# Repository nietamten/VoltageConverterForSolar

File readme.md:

Kicad project of NCP1034 based buck converter with features useful for solar panels and batteries.

After adjusting compensation network with "Design Spreadsheet for NCP1034" seems to be stable  
If it's not, see troubleshooting section.

There is separate output anode with current limit. It can be used simultaneously with that not limited.
For example battery can be charged with limiting (to not damage it by overcurrent) and some device can use non-limited anode to not distgurb charging.
It is not working ideally (limited output can limit that not limited) but can be helpfull.

Minimum input voltage limit can increase output power by keeping solar panels near maximum power point.
It can be regulated by applying load higher than solar panels power (or when panel are no well illuminated, but not too low illuminated because looses on BD911 regulator becomes dominant and then input voltages lower than at power point gives more power on output) and measuring output power.
Limiting screw should stay in position where power is highest.

NCP1034 have max 80% PWM duty cycle, all power can not pass throw.
Output diodes (D6 and D9) can be replaced with wire, but then converter allows power to flow in reverse direction. When there is no input volatge and on output is battery, battery can charge input capacitors and power on converter and cause losses. 

Assembly notices:
- read NCP1034 datasheet and use xls "design worksheet"
- BD911 gives off a lot of heat, don't ommit radiator, it will be damaged on 15V supply overload
For testing, when short circuits are possible, raplace BD911 based regulator with some other, more failproof
for example LM5008 based converter. Using LM5008 also significantly reduces heat of whole device on light loads.
- do not ommit 3x100nF capacitors on imput, it can cause instability
- current sensing resistor (R13, R16) limits maximum current, use lower resistance when more current is needed to not burn it
- RT pin resistor (R7) was tested between 22k and 47k (90-180kHz), lower resistance (higher frequency) makes more heat on NCP1034, BD911 and AOB414 but seems to improve stability
(I have oversized inductor). Setting too high frequency can very fast cause overheat and damage to NCP1034.
- Touching working converter parts near NCP1034 (for example to check heating) can easily cause damage of NCP1034 and AOB414. Especially overcurrent and soft start circuits.
- do not mount parts without values, for exaple C21

Troubleshooting:
- converter is oscillating fast (there is output power)
  - increase input capacity
  - add low ESR capacitors on input, for example ceramic
  - change frequency (R7)
- converter is oscillating slower (a little or no power on output)
  - decrease output capacity to prevent over current
  - increase current limit (decrease R11), 5k seems to be safe
  - decrease output volage
- converter is oscillating when minimum voltage limit is working
  - try increase C19 or C18
- converter is oscillating when current limiter is working
  - try increase C16 or experiment with C22
- devices near converter stops working (usb mouse)
  - use ferrite filters on input and output
 
Testing  
Device was tested with 4x parallel 75W 91VOC 67VMP solar panels on long wires.
The load was little 24V 300W water heater.
The heater was left on the whole sunny day in room temperature and stay not damagd.
Voltage on output was for some time about 27V so I suspect that it was more than 300W.
AOB414, BD911 and NCP1034 was very hot but below 100C. I'm not sure it can survive that load in higher ambient temperature.
With lighter loads (I'm guessing about 200W) BD911 is hottest. With LM5008 whole converter is only a little warm.

There is not completed automatic maximum power point tracking extension board with some measurments on UART 

V2 tagged version is better for self-made PCB's but have mistake - no resistor at output of  max input voltage limiting opamp.
V3 tagged verion is for PCB's with metalized holes, radiator for transistors can be on second PCB side.

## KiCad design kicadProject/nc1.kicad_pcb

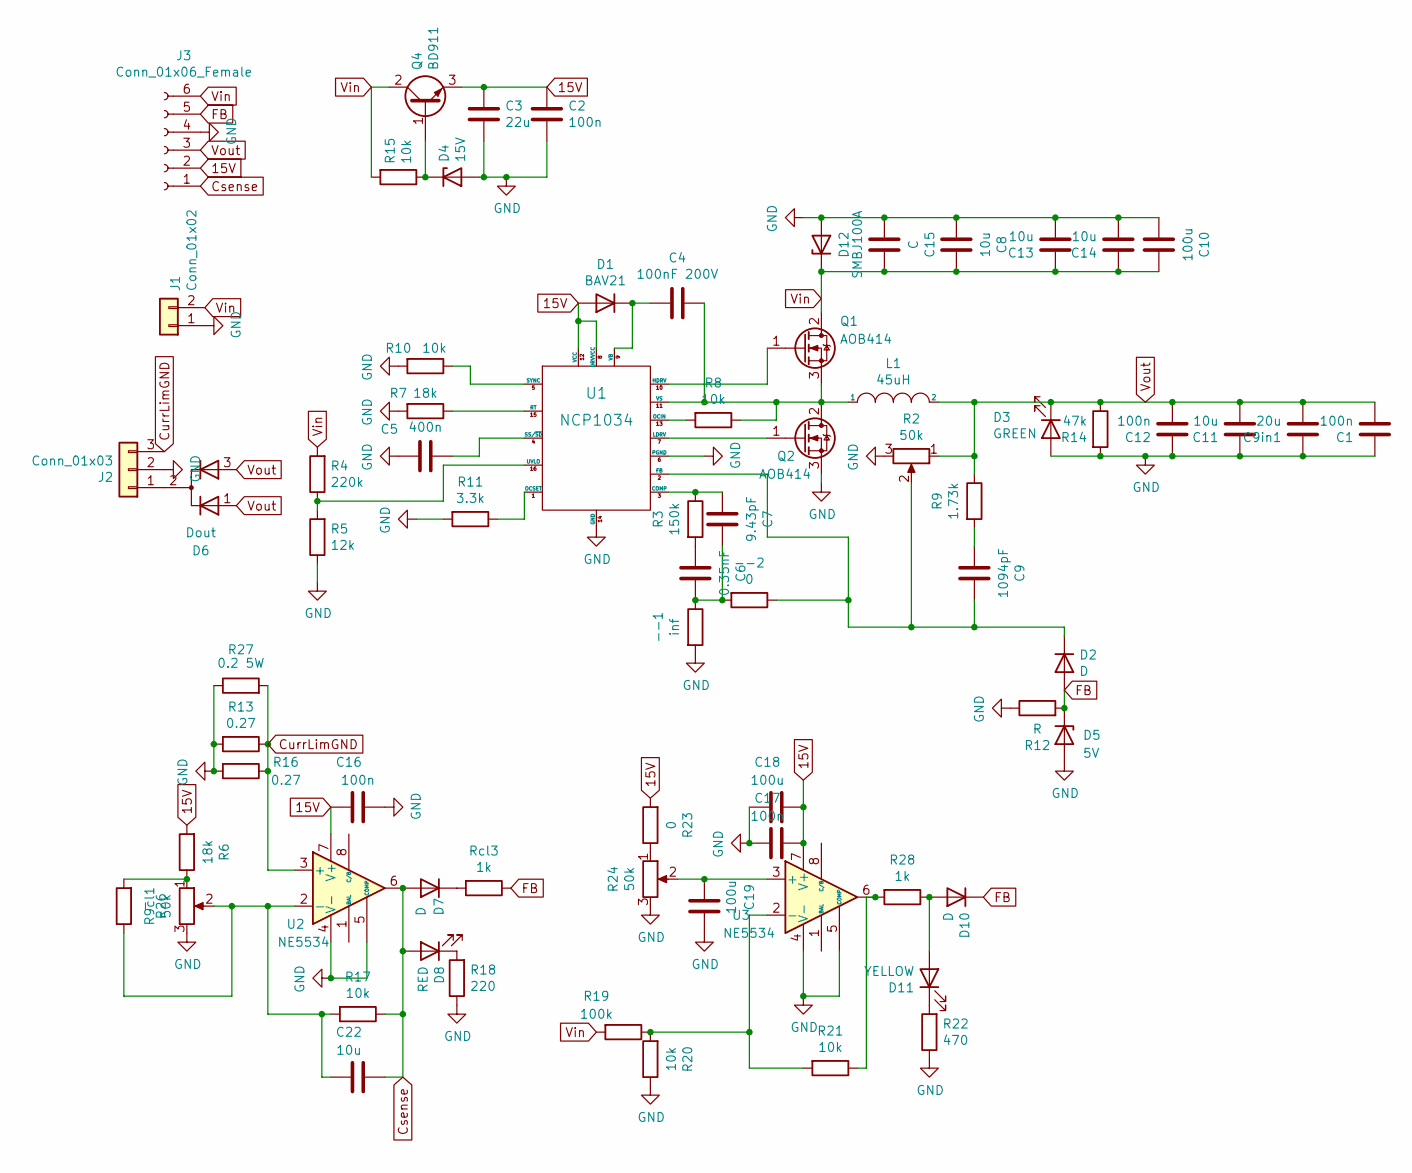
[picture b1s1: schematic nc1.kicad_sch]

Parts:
--1: inf; R_1206_3216Metric_Pad1.30x1.75mm_HandSolder
--2: 0; R_1206_3216Metric_Pad1.30x1.75mm_HandSolder
C1: 100n; CP_Radial_D18.0mm_P7.50mm
C2: 100n; C_1206_3216Metric
C3: 22u; C_1206_3216Metric
C4: 100nF 200V; C_2220_5650Metric
C5: 400n; C_1206_3216Metric_Pad1.42x1.75mm_HandSolder
C6: 0.35nF; C_1206_3216Metric_Pad1.42x1.75mm_HandSolder
C7: 9.43pF; C_1206_3216Metric_Pad1.42x1.75mm_HandSolder
C8: 10u; C_Rect_L7.0mm_W2.5mm_P5.00mm
C9: 1094pF; C_1206_3216Metric_Pad1.33x1.80mm_HandSolder
C9in1: 20u; C_Rect_L7.0mm_W2.5mm_P5.00mm
C10: 100u; C_Rect_L7.0mm_W2.5mm_P5.00mm
C11, C13, C14: 10u; CP_Radial_D16.0mm_P7.50mm
C12: 100n; C_Rect_L7.0mm_W2.5mm_P5.00mm
C15: C; C_Rect_L7.0mm_W2.5mm_P5.00mm
C16, C17: 100n; C_1206_3216Metric_Pad1.33x1.80mm_HandSolder
C18, C19: 100u; CP_Radial_D5.0mm_P2.50mm
C22: 10u; C_1206_3216Metric_Pad1.33x1.80mm_HandSolder
D1: BAV21; D_A-405_P10.16mm_Horizontal
D2, D7, D10: D; D_MiniMELF
D3: GREEN; LED_0805_2012Metric_Pad1.15x1.40mm_HandSolder
D4: 15V; D_MELF
D5: 5V; D_MELF
D6: Dout; TO-220-3_Vertical
D8: RED; LED_0805_2012Metric_Pad1.15x1.40mm_HandSolder
D11: YELLOW; LED_0805_2012Metric_Pad1.15x1.40mm_HandSolder
D12: SMBJ100A; D_SMB
J1: Conn_01x02; TerminalBlock_bornier-2_P5.08mm
J2: Conn_01x03; TerminalBlock_bornier-3_P5.08mm
J3: Conn_01x06_Female; PinHeader_1x06_P2.54mm_Vertical
L1: 45uH; L_Axial_L9.5mm_D4.0mm_P15.24mm_Horizontal_Fastron_SMCC
Q1, Q2: AOB414; TO-263-2
Q4: BD911; TO-220-3_Vertical
R2, R9cl1, R24: 50k; Potentiometer_Bourns_3296W_Vertical
R3: 150k; R_1206_3216Metric_Pad1.30x1.75mm_HandSolder
R4: 220k; R_1206_3216Metric_Pad1.30x1.75mm_HandSolder
R5: 12k; R_1206_3216Metric_Pad1.30x1.75mm_HandSolder
R6, R7: 18k; R_1206_3216Metric_Pad1.30x1.75mm_HandSolder
R8, R10, R17, R20, R21: 10k; R_1206_3216Metric_Pad1.30x1.75mm_HandSolder
R9: 1.73k; R_1206_3216Metric_Pad1.30x1.75mm_HandSolder
R11: 3.3k; R_1206_3216Metric_Pad1.30x1.75mm_HandSolder
R12: R; R_1206_3216Metric_Pad1.30x1.75mm_HandSolder
R13, R16: 0.27; R_2010_5025Metric_Pad1.40x2.65mm_HandSolder
R14: 47k; R_1206_3216Metric_Pad1.30x1.75mm_HandSolder
R15: 10k; R_Axial_DIN0207_L6.3mm_D2.5mm_P10.16mm_Horizontal
R18: 220; R_1206_3216Metric_Pad1.30x1.75mm_HandSolder
R19: 100k; R_1206_3216Metric_Pad1.30x1.75mm_HandSolder
R22: 470; R_1206_3216Metric_Pad1.30x1.75mm_HandSolder
R23: 0; R_1206_3216Metric_Pad1.30x1.75mm_HandSolder
R26: -; R_1206_3216Metric_Pad1.30x1.75mm_HandSolder
R27: 0.2 5W; R_Radial_Power_L16.1mm_W9.0mm_P7.37mm
R28: 1k; R_1206_3216Metric_Pad1.30x1.75mm_HandSolder
Rcl3: 1k; R_0805_2012Metric
U1: NCP1034; SOIC-16_3.9x9.9mm_P1.27mm
U2, U3: NE5534; SOIC-8_3.9x4.9mm_P1.27mm

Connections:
15V: C2.1, C3.1, C16.1, C17.2, C18.2, D1.2 (A), J3.2, Q4.3 (E), R6.2, R23.2, U1.8 (DRVVCC), U1.12 (VCC), U2.7 (V+), U3.7 (V+)
Csense: C22.2, D7.2 (A), D8.2 (A), J3.1, R17.1, U2.6
CurrLimGND: J2.3, R13.1, R16.1, R27.2, U2.3 (+)
FB: D2.2 (A), D5.1 (K), D10.1 (K), J3.5, R12.2, Rcl3.1
GND: --1.2, C1.2, C2.2, C3.2, C5.2, C8.2, C9in1.2, C10.2, C11.2, C12.2, C13.1, C14.1, C15.2, C16.2, C17.1, C18.1, C19.2, D3.2 (A), D4.2 (A), D5.2 (A), D12.2 (A), J1.1, J2.2, J3.4, Q2.3 (S), R2.3, R5.1, R7.2, R9cl1.3, R10.2, R11.2, R12.1, R13.2, R14.2, R16.2, R18.1, R20.1, R22.1, R24.3, R27.1, U1.6 (PGND), U1.14 (GND), U2.4 (V-), U2.5 (COMP), U3.4 (V-), U3.5 (COMP)
unnamed: --1.1, --2.2, C6.1, C7.1
unnamed: --2.1, C9.1, D2.1 (K), R2.2, U1.2 (FB)
unnamed: C4.1, L1.1, Q1.3 (S), Q2.2 (D), R8.1, U1.11 (VS)
unnamed: C4.2, D1.1 (K), U1.9 (VB)
unnamed: C5.1, U1.4 (SS/~SD)
unnamed: C6.2, R3.2
unnamed: C7.2, R3.1, U1.3 (COMP)
unnamed: C9.2, R9.2
unnamed: C19.1, R24.2, U3.3 (+)
unnamed: C22.1, R9cl1.2, R17.2, R26.1, U2.2 (-)
unnamed: D4.1 (K), Q4.1 (B), R15.1
unnamed: D7.1 (K), Rcl3.2
unnamed: D8.1 (K), R18.2
unnamed: D10.2 (A), D11.2 (A), R28.1
unnamed: D6.2 (A), J2.1
unnamed: Q1.1 (G), U1.10 (HDRV)
unnamed: Q2.1 (G), U1.7 (LDRV)
unnamed: R4.1, R5.2, U1.16 (UVLO)
unnamed: R7.1, U1.15 (RT)
unnamed: R8.2, U1.13 (OCIN)
unnamed: R11.1, U1.1 (OCSET)
unnamed: R19.1, R20.2, R21.2, U3.2 (-)
unnamed: R21.1, R28.2, U3.6
unnamed: D11.1 (K), R22.2
unnamed: R23.1, R24.1
unnamed: R6.1, R9cl1.1, R26.2
unnamed: R10.1, U1.5 (SYNC)
Vin: C8.1, C10.1, C13.2, C14.2, C15.1, D12.1 (K), J1.2, J3.6, Q1.2 (D), Q4.2 (C), R4.2, R15.2, R19.2
Vout: C1.1, C9in1.1, C11.1, C12.1, D3.1 (K), D6.1 (K), D6.3 (K), J3.3, L1.2, R2.1, R9.1, R14.1

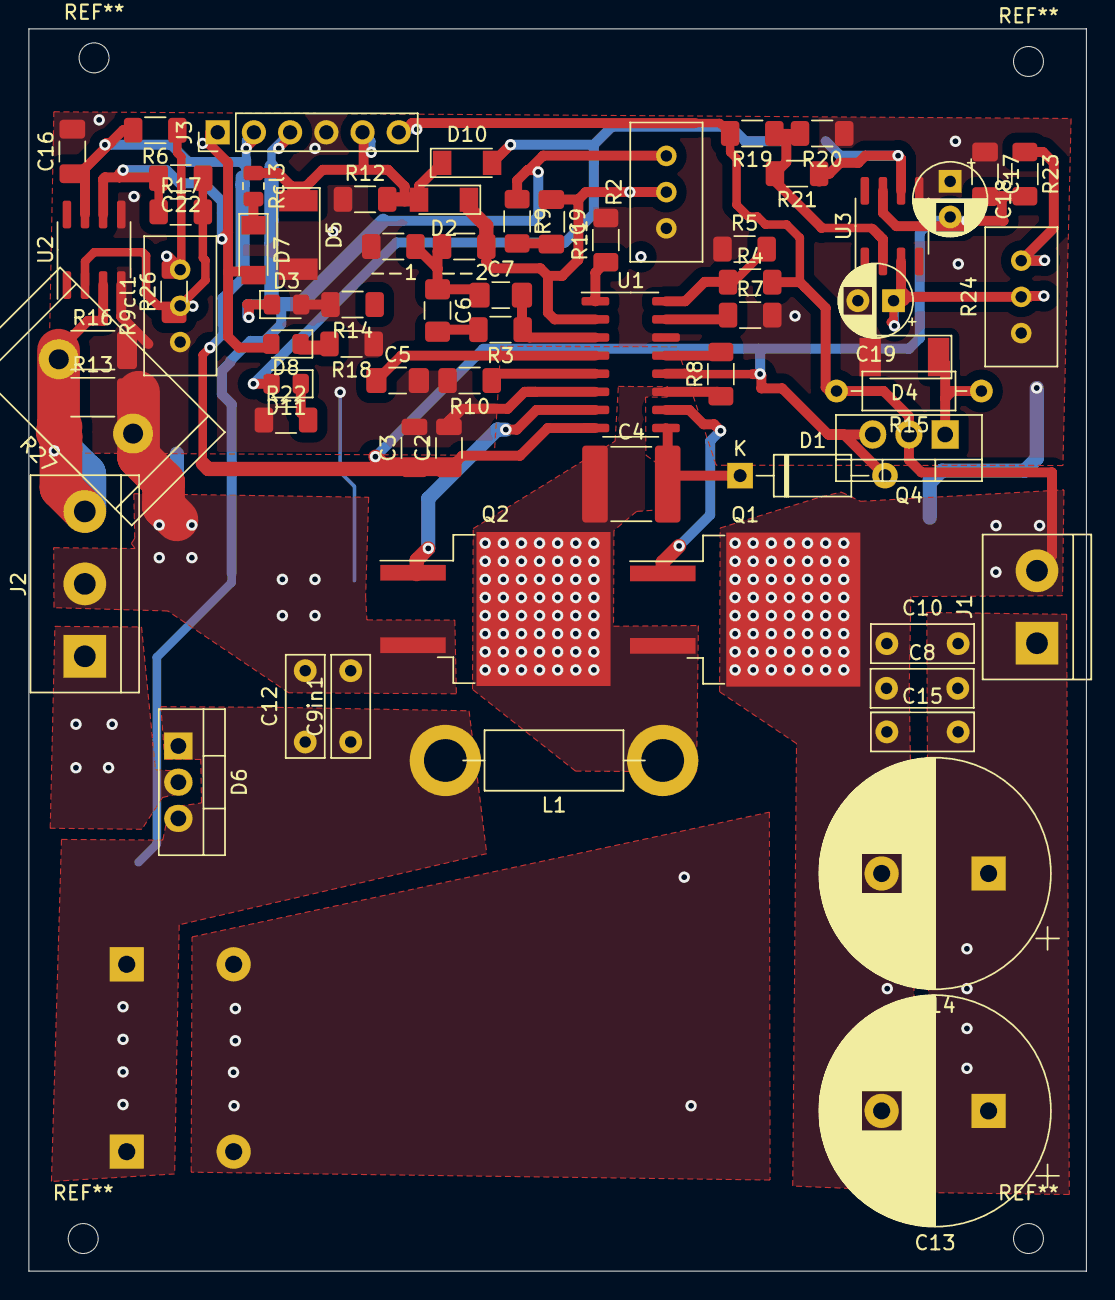
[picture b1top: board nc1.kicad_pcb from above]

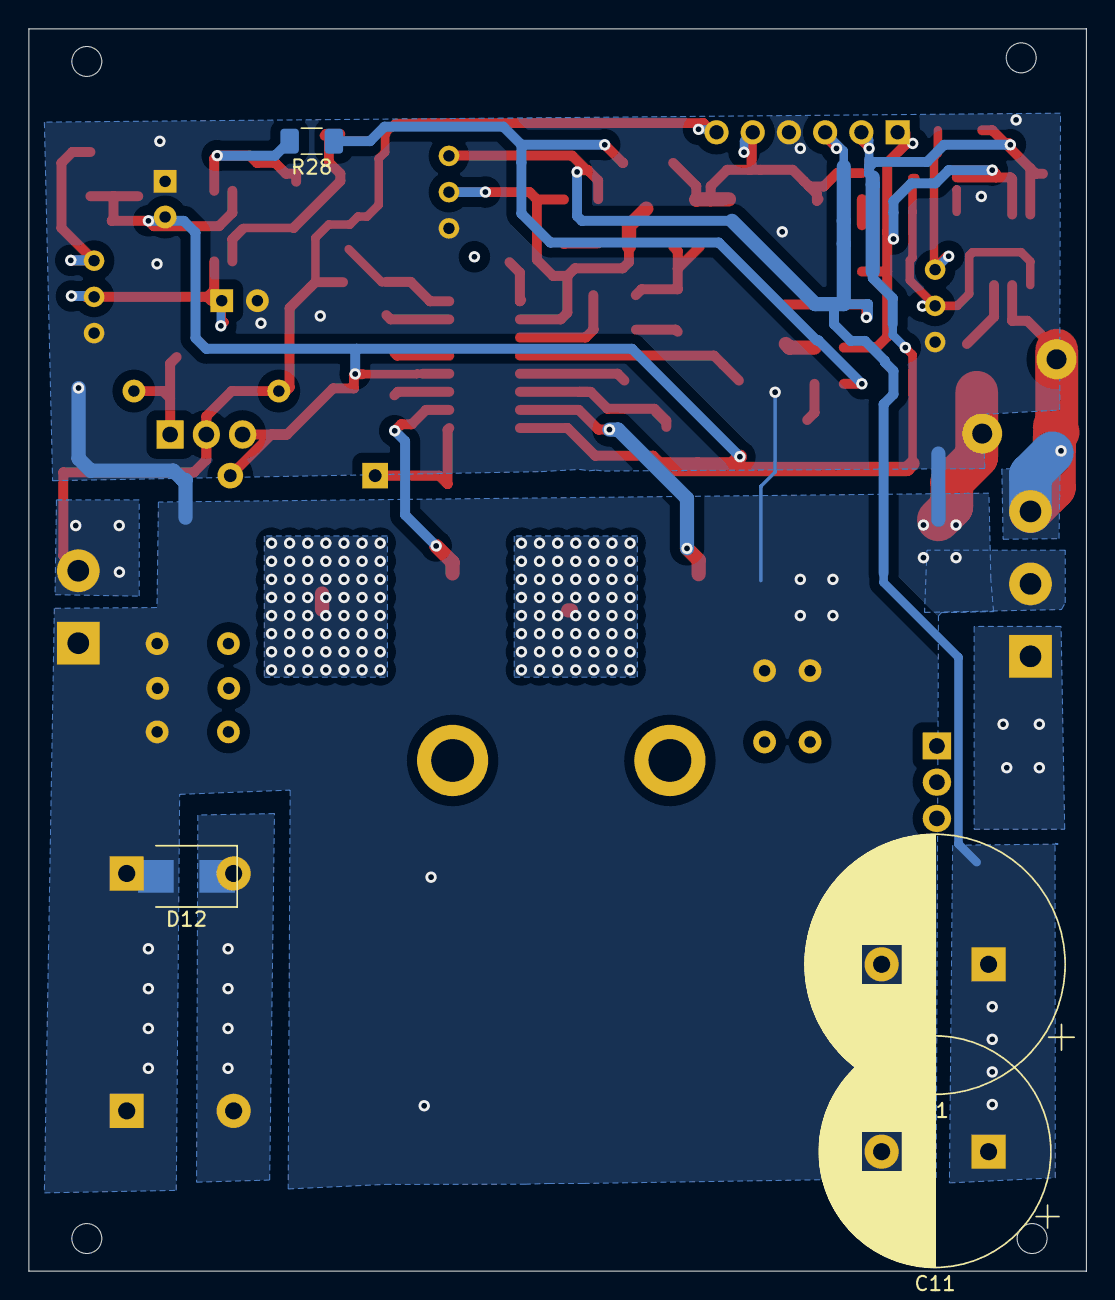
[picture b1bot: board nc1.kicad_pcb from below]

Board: 2 copper layers, 74.2 x 87.1 mm, 72 parts (4 on the bottom side), 34 nets.

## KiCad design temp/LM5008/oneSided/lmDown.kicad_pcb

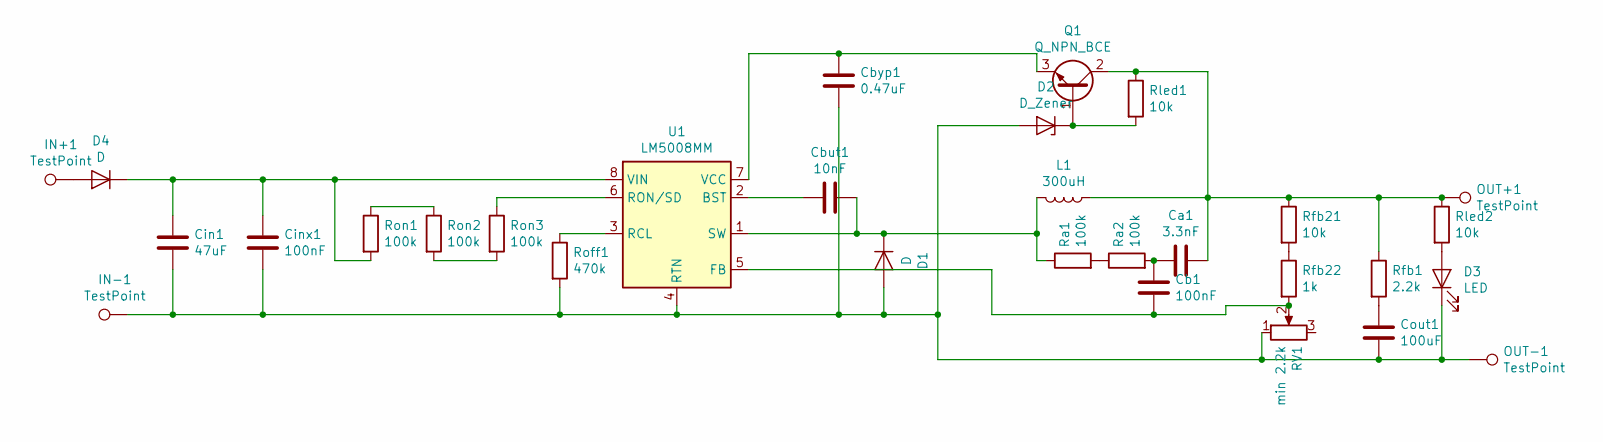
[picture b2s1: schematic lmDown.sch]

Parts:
Ca1: 3.3nF; C_1206_3216Metric_Pad1.42x1.75mm_HandSolder
Cb1: 100nF; C_1206_3216Metric_Pad1.42x1.75mm_HandSolder
Cbut1: 10nF; C_Disc_D7.5mm_W5.0mm_P5.00mm
Cbyp1: 0.47uF; C_0805_2012Metric_Pad1.15x1.40mm_HandSolder
Cin1: 47uF; CP_Radial_D8.0mm_P3.80mm
Cinx1: 100nF; C_Rect_L7.2mm_W3.5mm_P5.00mm_FKS2_FKP2_MKS2_MKP2
Cout1: 100uF; CP_Radial_D10.0mm_P5.00mm
D1: D; D_DO-15_P10.16mm_Horizontal
D2: D_Zener; D_1206_3216Metric
D3: LED; LED_0805_2012Metric
D4: D; D_A-405_P10.16mm_Horizontal
IN+1: TestPoint; TestPoint_Loop_D2.50mm_Drill1.85mm
IN-1: TestPoint; TestPoint_Loop_D2.50mm_Drill1.85mm
L1: 300uH; L_Radial_D10.0mm_P5.00mm_Fastron_07P
OUT+1: TestPoint; TestPoint_Loop_D2.50mm_Drill1.85mm
OUT-1: TestPoint; TestPoint_Loop_D2.50mm_Drill1.85mm
Q1: Q_NPN_BCE; TO-92L_Inline_Wide
RV1: min 2.2k; Potentiometer_Runtron_RM-065_Vertical
Ra1, Ra2: 100k; R_1206_3216Metric_Pad1.42x1.75mm_HandSolder
Rfb1: 2.2k; R_1206_3216Metric_Pad1.42x1.75mm_HandSolder
Rfb21: 10k; R_1206_3216Metric_Pad1.42x1.75mm_HandSolder
Rfb22: 1k; R_1206_3216Metric_Pad1.42x1.75mm_HandSolder
Rled1, Rled2: 10k; R_1206_3216Metric_Pad1.42x1.75mm_HandSolder
Roff1: 470k; R_1206_3216Metric_Pad1.42x1.75mm_HandSolder
Ron1, Ron2, Ron3: 100k; R_1206_3216Metric_Pad1.42x1.75mm_HandSolder
U1: LM5008MM; MSOP-8_3x3mm_P0.65mm

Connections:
unnamed: Ca1.1, L1.1, OUT+1.1, Q1.2 (C), Rfb1.1, Rfb21.1, Rled1.1, Rled2.1
unnamed: Ca1.2, Cb1.1, Ra2.2
unnamed: Cb1.2, RV1.2, Rfb22.2, U1.5 (FB)
unnamed: Cbut1.1, D1.1 (K), L1.2, Ra1.1, U1.1 (SW)
unnamed: Cbut1.2, U1.2 (BST)
unnamed: Cbyp1.1, Q1.3 (E), U1.7 (VCC)
unnamed: Cbyp1.2, Cin1.2, Cinx1.2, Cout1.2, D1.2 (A), D2.2 (A), D3.1 (K), IN-1.1, OUT-1.1, RV1.1, Roff1.2, U1.4 (RTN)
unnamed: Cin1.1, Cinx1.1, D4.1 (K), Ron1.2, U1.8 (VIN)
unnamed: Cout1.1, Rfb1.2
unnamed: D2.1 (K), Q1.1 (B), Rled1.2
unnamed: D3.2 (A), Rled2.2
unnamed: D4.2 (A), IN+1.1
unnamed: Ra1.2, Ra2.1
unnamed: Rfb21.2, Rfb22.1
unnamed: Roff1.1, U1.3 (RCL)
unnamed 16: Ron1.1, Ron2.1; also elsewhere on the board
unnamed 17: Ron2.2, Ron3.2; also elsewhere on the board
unnamed: Ron3.1, U1.6 (RON/SD)

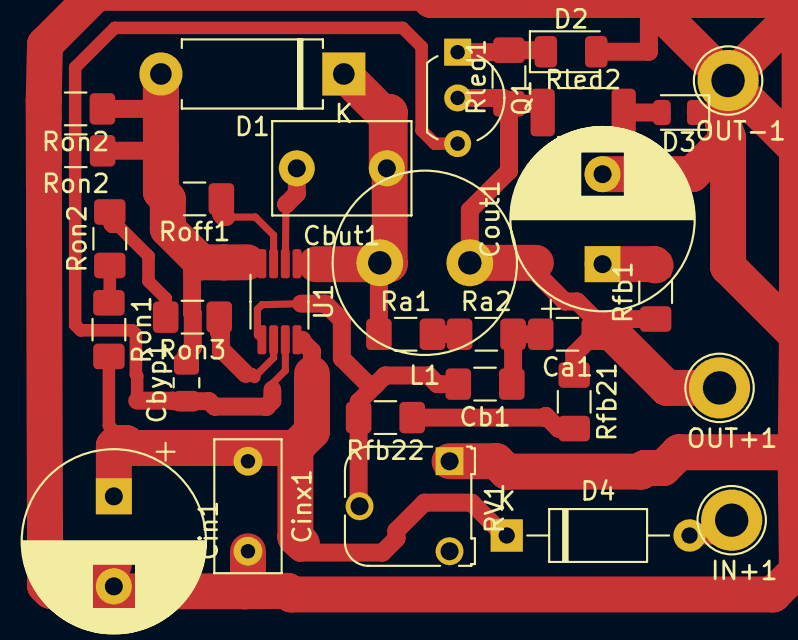
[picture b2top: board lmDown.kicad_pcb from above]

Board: 2 copper layers, 31 parts (0 on the bottom side), 18 nets.

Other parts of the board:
Ron2#2, Ron2#3: 100k; R_1206_3216Metric_Pad1.42x1.75mm_HandSolder

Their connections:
unnamed 16: Ron2#2.1, Ron2#3.1; also elsewhere on the board
unnamed 17: Ron2#2.2, Ron2#3.2; also elsewhere on the board

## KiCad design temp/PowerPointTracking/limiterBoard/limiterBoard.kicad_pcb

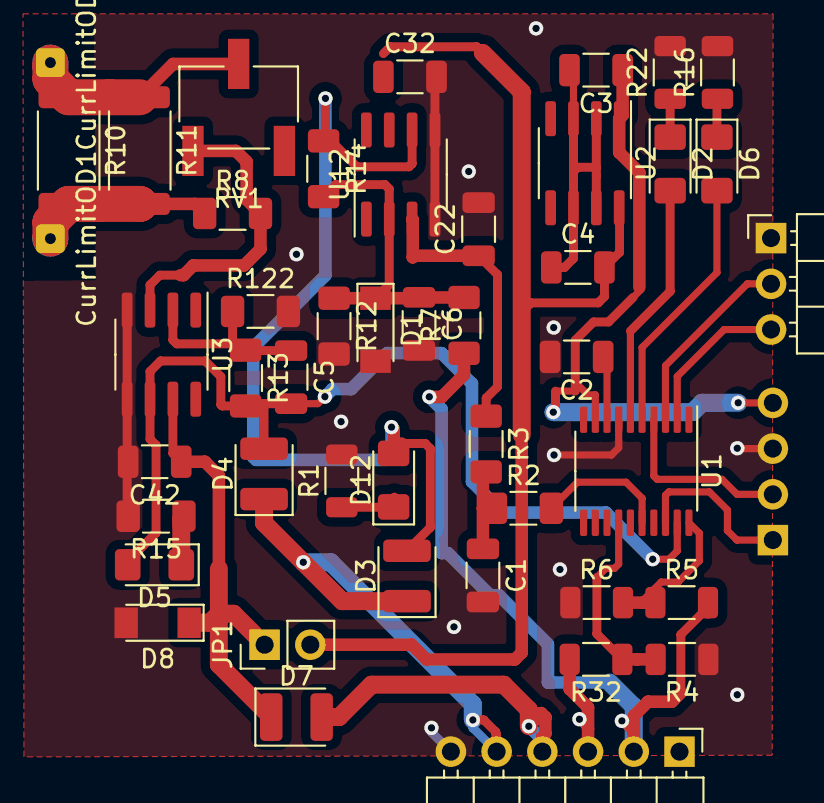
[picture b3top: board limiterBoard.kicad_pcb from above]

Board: 2 copper layers, 47 parts (1 on the bottom side), 32 nets.

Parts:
C1, C3, C5, C6, C22, C32, C42: 100n; C_1206_3216Metric
C2: 470-3300n; C_1206_3216Metric
C4: 0.33uf; C_1206_3216Metric
CurrLimitOD1: -LOAD; SolderWire-0.1sqmm_1x01_D0.4mm_OD1mm
CurrLimitOD2: GND_LOAD; SolderWire-0.1sqmm_1x01_D0.4mm_OD1mm
D1, D8: 5-15v; D_MiniMELF
D2, D6, D12: LED; LED_1206_3216Metric_Pad1.42x1.75mm_HandSolder
D3, D4, D7: D; D_1210_3225Metric
D5: GREEN; LED_1206_3216Metric_Pad1.42x1.75mm_HandSolder
J1: ST-LINK; PinHeader_1x04_P2.54mm_Horizontal
J2: UART; PinHeader_1x03_P2.54mm_Horizontal
J3: board; PinHeader_1x06_P2.54mm_Horizontal
JP1: Jumper_2_Open; PinHeader_1x02_P2.54mm_Vertical
R1, R16, R22: R; R_1206_3216Metric
R2, R3: 47k; R_1206_3216Metric_Pad1.30x1.75mm_HandSolder
R4, R6: 3.3k; R_1206_3216Metric
R5, R32: 100k; R_1206_3216Metric
R7: 29k; R_1206_3216Metric_Pad1.30x1.75mm_HandSolder
R8: 330; R_1206_3216Metric_Pad1.30x1.75mm_HandSolder
R10, R11: 0.27; R_2512_6332Metric
R12, R13: 1.5k; R_1206_3216Metric_Pad1.30x1.75mm_HandSolder
R14: 10k; R_1206_3216Metric_Pad1.30x1.75mm_HandSolder
R15: R; R_1206_3216Metric_Pad1.30x1.75mm_HandSolder
R122: 1.2k; R_1206_3216Metric_Pad1.30x1.75mm_HandSolder
RV1: 1k; Potentiometer_Bourns_3269W_Vertical
U1: STM8S003F3P; TSSOP-20_4.4x6.5mm_P0.65mm
U2: L78L05_SO8; SOIC-8_3.9x4.9mm_P1.27mm
U3, U12: NE5534; SOIC-8_3.9x4.9mm_P1.27mm

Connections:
+14PP: C4.2, C32.1, JP1.2, U2.8, U12.7
+14V: C42.1, D7.1, D8.1, JP1.1, U3.7
ADC1: R5.1, R6.2, U1.20
ADC2: R4.2, R32.1, U1.14
GND: C1.2, C2.2, C6.2, C22.2, C32.2, C42.2, D1.2, D8.2, J1.3, J2.1, J3.6, R1.2, R4.1, R6.1, R12.2, R15.2, R16.2, R22.2, R122.2, U1.7, U3.4, U3.5, U12.4, U12.5
unnamed: C1.1, R2.1, R3.2
unnamed: C2.1, U1.8
unnamed: C3.1, J1.4, U1.9, U2.1
unnamed: C3.2, C4.1, U2.2, U2.3, U2.6, U2.7
unnamed: C5.1, R13.1, R122.1, U3.2
unnamed: C5.2, D4.2, D5.2, R13.2, U1.19, U3.6
unnamed: C6.1, D1.1, R7.2, R12.1, R14.2, U12.2
unnamed: C22.1, R3.1, U12.3
unnamed: CurrLimitOD1.1, R8.1, R10.2, R11.2
unnamed: CurrLimitOD2.1, R10.1, R11.1, RV1.2
unnamed: D2.1, R22.1
unnamed: D2.2, U1.6
unnamed: D5.1, R15.1
unnamed: D6.1, R16.1
unnamed: D6.2, U1.5
unnamed: D7.2, J3.4
unnamed: D12.1, R1.1
unnamed: D3.2, D12.2, R14.1, U12.6
unnamed: J1.1, U1.18
unnamed: J1.2, U1.4
unnamed: J2.2, U1.3
unnamed: J2.3, U1.2
unnamed: J3.3, R32.2
unnamed: R8.2, RV1.1, U3.3
PWM1: R2.2, U1.16
PWMout: D3.1, D4.1, J3.5
Vin: J3.2, R5.2, R7.1

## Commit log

2021-03-31 Update readme.md
    more comments
2021-03-31 Update readme.md
    new line
2021-03-31 Update readme.md
    indentation
2021-03-31 fixes
2021-04-02 Update readme.md
    description fix
2021-04-03 Update readme.md
    fixes
2021-04-03 Update readme.md
    fix
2021-04-21 more compensatioon
2021-06-25 stability fixes
2021-06-25 readme fixes
2021-06-26 new photo
